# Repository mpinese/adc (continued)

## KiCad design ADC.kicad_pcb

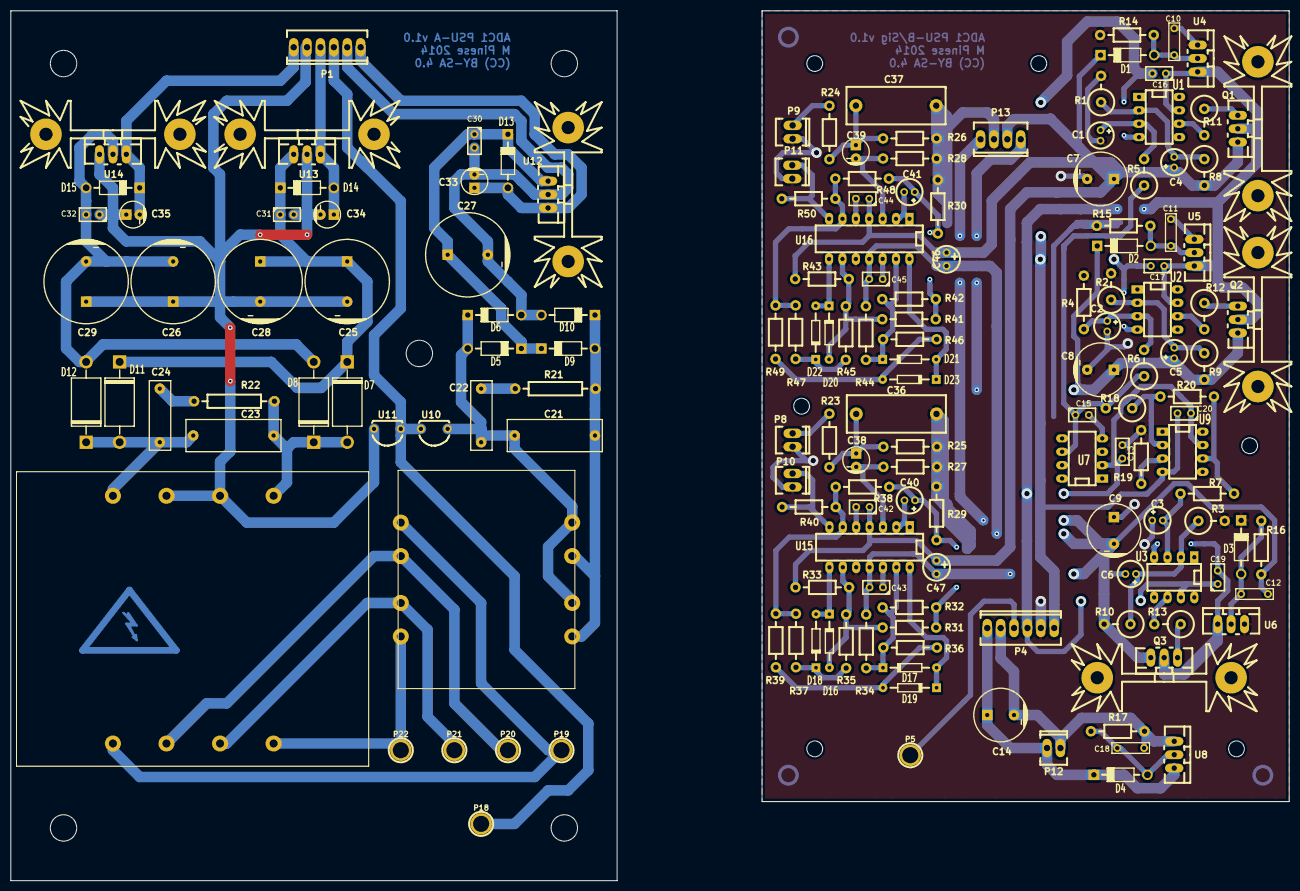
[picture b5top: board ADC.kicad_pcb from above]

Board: 4 copper layers, 242.5 x 165.0 mm, 188 parts (1 on the bottom side), 74 nets.

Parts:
C1, C3, C4, C5, C6: 10u; Elko_vert_DM5_RM2
C2, C40, C41: 47u; Elko_vert_DM5_RM2
C7, C8, C9, C14: 470u; Capacitor10x16RM5
C10, C11, C12, C18: 47n; Capacitor7.5MMDiscRM5
C13, C15, C16, C17, C19, C20, C30, C31, C32, C42, C43, C44, C45: 470n; Capacitor3MMDiscRM2.5
C21, C23: 150n; Capacitor18x6RM15
C22, C24: 10n; Capacitor13x4RM10
C25, C26, C27, C28, C29: 2700u; Capacitor16x25RM7.5
C33, C34, C35: 1u; Capacitor5x6RM2.5
C36, C37: 6.2n; Capacitor18x7RM15
C38, C39: 22u; Capacitor5x11RM2.5
C46, C47: 10u; Elko_vert_DM5_RM2-5
D1, D3: 1N4745; Diode_DO-41_SOD81_Horizontal_RM10
D2: 1N4731; Diode_DO-41_SOD81_Horizontal_RM10
D4: 1N4734; Diode_DO-41_SOD81_Horizontal_RM10
D5, D6, D9, D10, D13, D14, D15: 1N4001; Diode_DO-41_SOD81_Horizontal_RM10
D7, D8, D11, D12: RL205; Diode_DO-201AD_Horizontal_RM15
D16, D17, D18, D19, D20, D21, D22, D23: 1N4148; Diode_DO-35_SOD27_Horizontal_RM10
F1: FUSE; Dummy_Empty
FID: Fiducial_Modern_CopperBottom_RevC; Fiducial_Modern_CopperBottom
FID#2, FID#3: Fiducial_Modern_CopperBottom_RevC; Fiducial_Modern_CopperBottom
HS: Heatsink_Fischer_SK104-STC-STIC_35x13mm_2xDrill2.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; Heatsink_Fischer_SK104-STC-STIC_35x13mm_2xDrill2.5mm
HS#2, HS#3, HS#4, HS#5, HS#6: Heatsink_Fischer_SK104-STC-STIC_35x13mm_2xDrill2.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; Heatsink_Fischer_SK104-STC-STIC_35x13mm_2xDrill2.5mm
J1, J2: RCA; Dummy_Empty
J3: IEC-C13-SOCKET; Dummy_Empty
MH: MountingHole_5mm_RevA_Date21Jun2010; MountingHole_5mm
MH#2, MH#3, MH#4, MH#5: MountingHole_5mm_RevA_Date21Jun2010; MountingHole_5mm
MH#6, MH#7, MH#8, MH#9, MH#10, MH#11: MountingHole_3mm_RevA_Date21Jun2010; MountingHole_3mm
P1, P4: CONN_6; Socket_MOLEX-KK-RM2-54mm_Lock_6pin_straight
P2, P3: CONN_6; Dummy_Empty
P5, P18, P19, P20, P21, P22: CONN_1; 1pin
P6, P7, P14, P15, P16: CONN_2; Dummy_Empty
P8, P9, P10, P11, P12: CONN_2; Socket_MOLEX-KK-RM2-54mm_Lock_2pin_straight
P13: CONN_4; Socket_MOLEX-KK-RM2-54mm_Lock_4pin_straight
P17: CONN_4; Dummy_Empty
Q1, Q2: BD241A; TO-220_Neutral123_Vertical_LargePads
Q3: BD242; TO-220_Neutral123_Vertical_LargePads
R1, R2, R3, R9: 4.99k; Resistor_Vertical_RM5mm
R4, R14, R15, R16, R17: 1k; Resistor_Horizontal_RM10mm
R5: 3.32k; Resistor_Vertical_RM5mm
R6, R18: 1.5k; Resistor_Vertical_RM5mm
R7: 3.32k; Resistor_Horizontal_RM10mm
R8, R10: 10k; Resistor_Vertical_RM5mm
R11, R12, R13: 47; Resistor_Vertical_RM5mm
R19: 750; Resistor_Horizontal_RM10mm
R20: 1.5k; Resistor_Horizontal_RM10mm
R21, R22: R; Resistor_Horizontal_RM15mm
R23, R24: 56; Resistor_Horizontal_RM10mm
R25, R26, R27, R28, R29, R30: 22k; Resistor_Horizontal_RM10mm
R31, R32, R35, R36, R41, R42, R45, R46: 10k; Resistor_Horizontal_RM10mm
R33, R34, R43, R44: 24k; Resistor_Horizontal_RM10mm
R37, R38, R39, R40, R47, R48, R49, R50: 2.2k; Resistor_Horizontal_RM10mm
Sym: Symbol_Highvoltage_Type2_CopperTop_Small
T1: TRIAD-FS20-300-C2; TRIAD_FS16_400_C2
T2: TRIAD-FS48-750-C2; TRIAD_FS48_750_C2
U1, U2, U3, U9: OPA27; DIP-8__300_ELL
U4, U5, U6, U8: 2N6507; TO-220_Neutral123_Vertical_LargePads
U7: REF02; DIP-8__300_ELL
U10, U11: P0300ECL; TO-92-Free-inline-wide
U12: MC7805C; TO-220_Neutral123_Vertical_LargePads
U13: LM7818CT; TO-220_Neutral123_Vertical_LargePads
U14: LM7918CT; TO-220_Neutral123_Vertical_LargePads
U15, U16: LME49740; DIP-14__300_ELL

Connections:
/Clipper/+15V: C4.1, C7.1, C42.1, C44.1, C46.1, C47.1, D1.2, P13.2, Q1.3, R8.2, R33.2, R43.2, U15.4, U16.4
/Clipper/-15V: C6.2, C9.2, C12.2, C43.2, C45.2, C46.2, C47.2, P13.4, Q3.3, R10.2, R16.2, R34.1, R44.1, U15.11, U16.11
/Clipper/AGND: C1.2, C2.2, C3.1, C7.2, C8.2, C9.1, C10.2, C11.2, C13.2, C15.2, C36.2, C37.2, C42.2, C43.1, C44.2, C45.1, D3.2, P4.5, P8.2, P9.2, P10.2, P11.2, P13.3, R1.2, R2.2, R3.2, R4.2, R14.2, R15.2, R19.2, R25.2, R26.2, R27.2, R28.2, R29.2, R30.2, U4.1, U5.1, U6.3, U7.4, U15.5, U15.10, U15.12, U16.5, U16.10, U16.12
/Clipper/LIN: C40.1, R29.1, R31.1, R32.1, R38.1
/Clipper/LOUT: P10.1, R40.2, U15.7
/Clipper/RIN: C41.1, R30.1, R41.1, R42.1, R48.1
/Clipper/ROUT: P11.1, R50.2, U16.7
/Line Receiver/LIN: P8.1, R23.1
/Line Receiver/RIN: P9.1, R24.1
/PSU-external/+5V_EXT: C33.1, D13.1, P1.1, U12.3
/PSU-external/+18V_EXT: C34.1, D14.1, P1.4, U13.3
/PSU-external/-18V_EXT: C35.2, D15.2, P1.6, U14.3
/PSU-external/AGND_EXT: C25.2, C26.1, C28.2, C29.1, C31.2, C32.1, C34.2, C35.1, P1.5, T2.6, T2.7, U11.3, U13.2, U14.1
/PSU-external/DGND_EXT: C27.2, C30.2, C33.2, D6.1, D10.1, P1.2, U12.2
/PSU-external/PA1: P19.1, T1.1, T2.1
/PSU-external/PA2: P20.1, T1.2, T2.2
/PSU-external/PB1: P21.1, T1.3, T2.3
/PSU-external/PB2: P22.1, T1.4, T2.4
/PSU-external/SAF_GND: P1.3, P18.1, U10.3, U11.1
/PSU-external/SEC1: C23.2, C24.2, D11.1, D12.2, T2.5
/PSU-external/SEC2: C23.1, D7.1, D8.2, R22.2, T2.8
/PSU-external/SEC3: C21.2, C22.2, D5.1, D6.2, T1.5, T1.7, U10.1
/PSU-external/SEC4: C21.1, D9.1, D10.2, R21.2, T1.6, T1.8
/PSU-external/SEC6: C22.1, R21.1
/PSU-external/SEC7: C24.1, R22.1
/PSU-internal/+4V: C5.1, C8.1, D2.2, P13.1, Q2.3, R9.2
/PSU-internal/+5V: C14.1, D4.2, P4.1, P12.1, U8.3
/PSU-internal/+18V_EXT: C13.1, C16.1, C17.1, C19.1, C20.1, P4.4, Q1.2, Q2.2, U1.7, U2.7, U3.7, U4.3, U5.3, U7.2, U9.7
/PSU-internal/-18V_EXT: C16.2, C17.2, C19.2, C20.2, P4.6, Q3.2, U1.4, U2.4, U3.4, U6.1, U9.4
/PSU-internal/DGND: C14.2, C18.2, P4.2, P12.2, R17.2, U8.1
/PSU-internal/VREF+: C15.1, R5.1, R6.1, R18.2, U7.6
/PSU-internal/VREF-: R7.1, R20.1, U9.6
unnamed: C1.1, R5.2, U1.3
unnamed: C2.1, R4.1, R6.2, U2.3
unnamed: C3.2, R7.2, U3.3
unnamed: C4.2, R1.1, R8.1, U1.2
unnamed: C5.2, R2.1, R9.1, U2.2
unnamed: C6.1, R3.1, R10.1, U3.2
unnamed: C10.1, D1.1, R14.1, U4.2
unnamed: C11.1, D2.1, R15.1, U5.2
unnamed: C12.1, D3.1, R16.1, U6.2
unnamed: C18.1, D4.1, R17.1, U8.2
unnamed: C25.1, C28.1, C31.1, D7.2, D11.2, D14.2, U13.1
unnamed: C26.2, C29.2, C32.2, D8.1, D12.1, D15.1, U14.2
unnamed: C27.1, C30.1, D5.2, D9.2, D13.2, U12.1
unnamed: C36.1, C38.1, R23.2, R25.1
unnamed: C37.1, C39.1, R24.2, R26.1
unnamed: C38.2, R27.1, U15.3
unnamed: C39.2, R28.1, U16.3
unnamed: C40.2, U15.1, U15.2
unnamed: C41.2, U16.1, U16.2
unnamed: D16.1, R31.2, R33.1, R35.1, U15.9
unnamed: D16.2, D18.1, U15.8
unnamed: D17.1, D19.2, U15.14
unnamed: D17.2, R32.2, R34.2, R36.1, U15.13
unnamed: D18.2, R35.2, R37.1
unnamed: D19.1, R36.2, R39.1
unnamed: D20.1, R41.2, R43.1, R45.1, U16.9
unnamed: D20.2, D22.1, U16.8
unnamed: D21.1, D23.2, U16.14
unnamed: D21.2, R42.2, R44.2, R46.1, U16.13
unnamed: D22.2, R45.2, R47.1
unnamed: D23.1, R46.2, R49.1
unnamed: P4.3, P5.1
unnamed: Q1.1, R11.1
unnamed: Q2.1, R12.1
unnamed: Q3.1, R13.1
unnamed: R11.2, U1.6
unnamed: R12.2, U2.6
unnamed: R13.2, U3.6
unnamed: R18.1, R20.2, U9.2
unnamed: R19.1, U9.3
unnamed: R37.2, R38.2, R39.2, R40.1, U15.6
unnamed: R47.2, R48.2, R49.2, R50.1, U16.6

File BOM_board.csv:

"Id";"Designator";"Package";"Quantity";"Designation";"Supplier and ref";
1;"MH,MH,MH,MH,MH";"Mounting_Holes:MountingHole_5mm";5;"MountingHole_5mm_RevA_Date21Jun2010";;;
2;"C1,C3,C4,C5,C6";"Capacitors_Elko_ThroughHole:Elko_vert_DM5_RM2";5;"10u";;;
3;"C2,C40,C41";"Capacitors_Elko_ThroughHole:Elko_vert_DM5_RM2";3;"47u";;;
4;"C7,C8,C9,C14";"Capacitors_ThroughHole:Capacitor10x16RM5";4;"470u";;;
5;"C10,C11,C12,C18";"Capacitors_ThroughHole:Capacitor7.5MMDiscRM5";4;"47n";;;
6;"C13,C15,C16,C17,C19,C20,C30,C31,C32,C42,C43,C44,C45";"Capacitors_ThroughHole:Capacitor3MMDiscRM2.5";13;"470n";;;
7;"C21,C23";"Capacitors_ThroughHole:Capacitor18x6RM15";2;"150n";;;
8;"C22,C24";"Capacitors_ThroughHole:Capacitor13x4RM10";2;"10n";;;
9;"C25,C26,C27,C28,C29";"Capacitors_ThroughHole:Capacitor16x25RM7.5";5;"2700u";;;
10;"C33,C34,C35";"Capacitors_ThroughHole:Capacitor5x6RM2.5";3;"1u";;;
11;"C36,C37";"Capacitors_ThroughHole:Capacitor18x7RM15";2;"6.2n";;;
12;"C38,C39";"Capacitors_ThroughHole:Capacitor5x11RM2.5";2;"22u";;;
13;"D1,D3";"Diodes_ThroughHole:Diode_DO-41_SOD81_Horizontal_RM10";2;"1N4745";;;
14;"D2";"Diodes_ThroughHole:Diode_DO-41_SOD81_Horizontal_RM10";1;"1N4731";;;
15;"D4";"Diodes_ThroughHole:Diode_DO-41_SOD81_Horizontal_RM10";1;"1N4734";;;
16;"D5,D6,D9,D10,D13,D14,D15";"Diodes_ThroughHole:Diode_DO-41_SOD81_Horizontal_RM10";7;"1N4001";;;
17;"D7,D8,D11,D12";"Diodes_ThroughHole:Diode_DO-201AD_Horizontal_RM15";4;"RL205";;;
18;"D16,D17,D18,D19,D20,D21,D22,D23";"Diodes_ThroughHole:Diode_DO-35_SOD27_Horizontal_RM10";8;"1N4148";;;
19;"P1,P4";"Sockets_MOLEX_KK-System:Socket_MOLEX-KK-RM2-54mm_Lock_6pin_straight";2;"CONN_6";;;
20;"P5,P18,P19,P20,P21,P22";"Connect:1pin";6;"CONN_1";;;
21;"P8,P9,P10,P11,P12";"Sockets_MOLEX_KK-System:Socket_MOLEX-KK-RM2-54mm_Lock_2pin_straight";5;"CONN_2";;;
22;"P13";"Sockets_MOLEX_KK-System:Socket_MOLEX-KK-RM2-54mm_Lock_4pin_straight";1;"CONN_4";;;
23;"Q1,Q2";"Transistors_TO-220:TO-220_Neutral123_Vertical_LargePads";2;"BD241A";;;
24;"Q3";"Transistors_TO-220:TO-220_Neutral123_Vertical_LargePads";1;"BD242";;;
25;"R15,R16,R17,R4,R14";"Resistors_ThroughHole:Resistor_Horizontal_RM10mm";5;"1k";;;
26;"R19";"Resistors_ThroughHole:Resistor_Horizontal_RM10mm";1;"750";;;
27;"R20";"Resistors_ThroughHole:Resistor_Horizontal_RM10mm";1;"1.5k";;;
28;"R21,R22";"Resistors_ThroughHole:Resistor_Horizontal_RM15mm";2;"R";;;
29;"R23,R24";"Resistors_ThroughHole:Resistor_Horizontal_RM10mm";2;"56";;;
30;"R25,R26,R27,R28,R29,R30";"Resistors_ThroughHole:Resistor_Horizontal_RM10mm";6;"22k";;;
31;"R31,R32,R35,R36,R41,R42,R45,R46";"Resistors_ThroughHole:Resistor_Horizontal_RM10mm";8;"10k";;;
32;"R37,R38,R39,R40,R47,R48,R49,R50";"Resistors_ThroughHole:Resistor_Horizontal_RM10mm";8;"2.2k";;;
33;"R43,R44,R34,R33";"Resistors_ThroughHole:Resistor_Horizontal_RM10mm";4;"24k";;;
34;"T1";"my-trafos:TRIAD_FS16_400_C2";1;"TRIAD-FS20-300-C2";;;
35;"T2";"my-trafos:TRIAD_FS48_750_C2";1;"TRIAD-FS48-750-C2";;;
36;"U4,U5,U6,U8";"Transistors_TO-220:TO-220_Neutral123_Vertical_LargePads";4;"2N6507";;;
37;"U7";"Sockets_DIP:DIP-8__300_ELL";1;"REF02";;;
38;"U10,U11";"Housings_TO-92:TO-92-Free-inline-wide";2;"P0300ECL";;;
39;"U12";"Transistors_TO-220:TO-220_Neutral123_Vertical_LargePads";1;"MC7805C";;;
40;"U13";"Transistors_TO-220:TO-220_Neutral123_Vertical_LargePads";1;"LM7818CT";;;
41;"U14";"Transistors_TO-220:TO-220_Neutral123_Vertical_LargePads";1;"LM7918CT";;;
42;"U15,U16";"Sockets_DIP:DIP-14__300_ELL";2;"LME49740";;;
43;"HS,HS,HS,HS,HS,HS";"Heatsinks:Heatsink_Fischer_SK104-STC-STIC_35x13mm_2xDrill2.5mm";6;"Heatsink_Fischer_SK104-STC-STIC_35x13mm_2xDrill2.5mm";;;
44;"Sym";"Footprint_Symbols:Symbol_Highvoltage_Type2_CopperTop_Small";1;"Symbol_Highvoltage_Type2_CopperTop_Small";;;
45;"U1,U2,U3,U9";"Sockets_DIP:DIP-8__300_ELL";4;"OPA27";;;
46;"R11,R13,R12";"Resistors_ThroughHole:Resistor_Vertical_RM5mm";3;"47";;;
47;"R8,R10";"Resistors_ThroughHole:Resistor_Vertical_RM5mm";2;"10k";;;
48;"R1,R3,R9,R2";"Resistors_ThroughHole:Resistor_Vertical_RM5mm";4;"4.99k";;;
49;"R5";"Resistors_ThroughHole:Resistor_Vertical_RM5mm";1;"3.32k";;;
50;"R6,R18";"Resistors_ThroughHole:Resistor_Vertical_RM5mm";2;"1.5k";;;
51;"R7";"Resistors_ThroughHole:Resistor_Horizontal_RM10mm";1;"3.32k";;;
52;"C46,C47";"Capacitors_Elko_ThroughHole:Elko_vert_DM5_RM2-5";2;"10u";;;
53;"MH,MH,MH,MH,MH,MH";"Mounting_Holes:MountingHole_3mm";6;"MountingHole_3mm_RevA_Date21Jun2010";;;
54;"FID,FID,FID";"Fiducials:Fiducial_Modern_CopperBottom";3;"Fiducial_Modern_CopperBottom_RevC";;;
55;"F1";"Oddities:Dummy_Empty";1;"FUSE";;;
56;"J1,J2";"Oddities:Dummy_Empty";2;"RCA";;;
57;"J3";"Oddities:Dummy_Empty";1;"IEC-C13-SOCKET";;;
58;"P2,P3";"Oddities:Dummy_Empty";2;"CONN_6";;;
59;"P6,P7,P14,P15,P16";"Oddities:Dummy_Empty";5;"CONN_2";;;
60;"P17";"Oddities:Dummy_Empty";1;"CONN_4";;;

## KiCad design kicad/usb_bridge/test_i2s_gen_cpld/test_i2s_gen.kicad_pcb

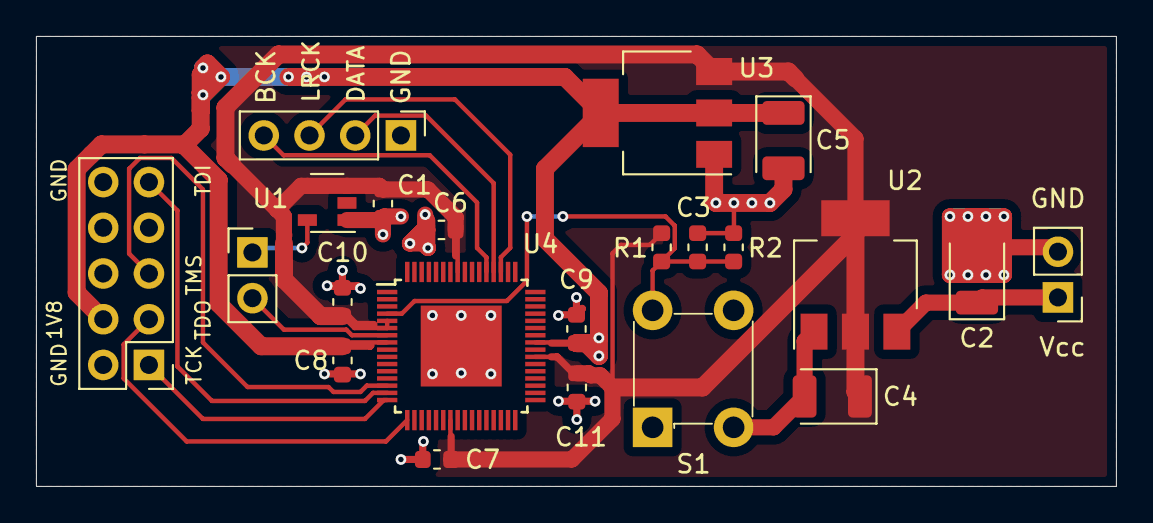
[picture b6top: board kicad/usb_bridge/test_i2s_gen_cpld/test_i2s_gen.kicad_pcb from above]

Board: 2 copper layers, 60.0 x 25.0 mm, 22 parts (0 on the bottom side), 14 nets.

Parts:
C1, C6, C7, C8, C9, C10, C11: 100n; C_0603_1608Metric
C2, C4, C5: CP; CP_EIA-3528-21_Kemet-B
C3: 470n; C_0603_1608Metric
J1, J3: Conn_01x02_Male; PinHeader_1x02_P2.54mm_Vertical
J2: Conn_02x05_Odd_Even; PinHeader_2x05_P2.54mm_Vertical
J4: Conn_01x04_Male; PinHeader_1x04_P2.54mm_Vertical
R1: 14k; R_0603_1608Metric
R2: 21k; R_0603_1608Metric
S1: 1825910-6; Switch_Tactile_THT_6x6mm
U1: SIT2001B; SOT-23-5
U2: AMS1117-3.3; SOT-223-3_TabPin2
U3: AMS1117-1.8; SOT-223-3_TabPin2
U4: 5M40ZE64C5N; TQFP-64_7x7mm_P0.4mm_EP4.5x4.5mm

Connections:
+1V8: C5.1, C8.1, C9.1, J2.4, U3.2, U4.8, U4.41
+3V3: C1.1, C4.1, C6.1, C7.1, C10.1, C11.1, R1.2, U1.3, U1.4, U2.2, U3.3, U4.5, U4.6, U4.23, U4.39, U4.57
/BCK: J4.4, U4.53
/CLK12: J3.2, U4.7
/DATA: J4.2, U4.52
/LRCK: J4.3, U4.51
/TCK: J2.1, U4.16
/TDI: J2.9, U4.15
/TDO: J2.3, U4.17
/TMS: J2.5, U4.14
/Vcc: C2.1, J1.1, U2.3
/~RESET: C3.1, R1.1, R2.2, S1.2, U4.4
GNDD: C1.2, C2.2, C3.2, C4.2, C5.2, C6.2, C7.2, C8.2, C9.2, C10.2, C11.2, J1.2, J2.2, J2.10, J4.1, R2.1, S1.3, S1.4, U1.1, U2.1, U3.1, U4.65
unnamed: J3.1, U1.5

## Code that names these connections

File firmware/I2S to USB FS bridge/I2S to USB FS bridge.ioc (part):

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Mcu.Name=STM32F730R8Tx
Mcu.Package=LQFP64
Mcu.UserName=STM32F730R8Tx
PA11.Mode=Device_Only
PA11.Signal=USB_OTG_FS_DM
PA12.Mode=Device_Only
PA12.Signal=USB_OTG_FS_DP
PA13.Mode=Serial_Wire
PA13.Signal=SYS_JTMS-SWDIO
PA14.Mode=Serial_Wire
PA14.Signal=SYS_JTCK-SWCLK
PA2.Mode=Asynchronous
PA2.Signal=USART2_TX
PA3.Mode=Asynchronous
PA3.Signal=USART2_RX
PA9.Mode=Activate_VBUS
PA9.Signal=USB_OTG_FS_VBUS
PB10.Mode=Half_Duplex_Slave
PB10.Signal=I2S2_CK
PB12.Mode=Half_Duplex_Slave
PB12.Signal=I2S2_WS
PC1.Mode=Half_Duplex_Slave
PC1.Signal=I2S2_SD
PC6.Signal=GPIO_Output
PC7.Signal=GPIO_Output
PC8.Signal=GPIO_Output
PC9.Signal=GPIO_Output
PH0-OSC_IN.Mode=HSE-External-Clock-Source
PH0-OSC_IN.Signal=RCC_OSC_IN
PH1-OSC_OUT.Mode=HSE-External-Clock-Source
PH1-OSC_OUT.Signal=RCC_OSC_OUT
RCC.HSE_VALUE=16000000
RCC.SYSCLKFreq_VALUE=216000000
RCC.SYSCLKSource=RCC_SYSCLKSOURCE_PLLCLK
board=custom

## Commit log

2014-05-04 Initial commit. Power supply mostly done; nothing else.
2014-05-04 Added the library cache file.
2014-05-05 Started on parts selection.
2014-05-06 Started work on changing the PSU to fully complementary.
2014-05-06 Started splitting the PSU into internal and external subsections.
2014-05-07 Simplified external PSU, now that I've decided to put it in its own case.
2014-05-09 Added an analysis of the low pass filter present in the PCM4222EVM differential input stage.
2014-05-10 Completed the overall system layout, added clipping and input stages.
2014-05-10 Further PSU tweaking for extra safety, added a TODO list.
2014-05-12 Expanded the internal PSU to include a 4 V supply. Started on reference sharing.
2014-05-12 Cleaned up the internal PSU a bit.
2014-05-15 Many additions; the system's almost together. Just need to tidy up a few things around the PSU and the input stage.
2014-05-21 First complete system. Still a few things to check.
2014-05-21 Noise analysis completed; signal section finished.
2014-05-21 V1.0 Schematic Completed.
2014-05-21 Added tag Schematic 1.0 for changeset 5b91ce586c58
2014-05-21 Added component numbers.
2014-05-21 Removed tag Schematic 1.0
2014-05-21 Added tag 1.0 Schematic for changeset b9613084385d
2014-05-21 Removed tag 1.0 Schematic
2014-05-21 Started specifying packages.
2014-05-21 More packages specified; changed the external PSU overvoltage protection devices.
2014-05-21 More packages specified.
2014-05-22 Minor schematic mods, started assigning DigiKey part numbers to components.
2014-05-22 Added more DigiKey catalogue numbers.
2014-05-23 Minor changes to noise sim.
2014-05-23 Further component specifications for the BOM.
2014-05-26 More components specified
2014-05-28 Completed component product code specification; started on footprints.
2014-05-29 Moved to new version of KiCad with updated footprints. Changed most of the footprints to match.
2014-05-29 Specified a few more components. These aren't perfect matches, but should do.
2014-05-30 Added internal connectors; specified all footprints and part IDs except for the trafos.
2014-05-30 More footprint specification and connector additions; almost done.
2014-05-31 Changed from the P0720ECL SIDACtor to the more sensitive P0300.
2014-05-31 Changed to use the fixed IEC socket device; the PSU netlist should now be (more) correct.
2014-06-01 A lot of routing, some parts changes: * Added snubber C/RC snubbers to transformer secondaries. * Changed PSU OA from OPA209 to OPA27. * Routed external PSU. * Mostly done routing internal circuits. 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
2014-06-02 First complete version. * Added 10uF decoupling capacitors to the start of each signal processing section. * Completed routing. A few -18 V nets remain unrouted; these will be wired in.
2014-06-03 Routed the -18 V line, added licence and descriptive text.
2014-06-03 Started work on a print SVG of the board layout.
2014-06-04 Added vias for ground-connected pins that cannot be soldered from the top, as I can't make PTHs. Rearranged the power inputs slightly.
2014-06-04 Filled in the ground plane this time -- oops!
2014-06-04 Minor ground rerouting.
2014-06-06 Collected layouts into a transparency svg. Created board and schematic BOMs (these still need to be fused)
2014-06-08 Moved component designators on silkscreen so that they are not covered by components. Combined silkscreen and user top layers into a cover layer for printing.
2014-06-09 Created script to collate final BOM.
2020-09-04 Update to 2020!
2020-09-04 Cleaning
2020-09-04 Fixed gitignore Tina-TI autosave exclusion
2020-09-11 Schematic bugfixes
2020-09-11 Firmware initial commit
2020-09-11 Cleaning up
2020-09-11 Attempted USB fixes
2020-09-12 ^&*%#$^&* copy-pasta!!!!
2020-09-13 Started adding class functionality.
2020-09-13 Restored GetHSConfigDescriptor, which seems to be necessary for successful enum (on Win10 at least).
2020-09-13 Added basic control signals.
2020-09-15 Started writing state machine for main I2S -> USB controller.
2020-09-15 More state machine work.
2020-09-15 Switched to left-justified audio input
2020-09-18 Added I2S test signal generator circuit.
2020-09-18 Added debug messages to USB loop.
2020-09-18 Added preregs to all rails.
2020-09-21 Started changing test generator to CPLD design
2020-09-21 Added TODO to enclosure SVG
2020-09-21 Restored serial audio test generator discrete design from #cee2e1e
2020-09-29 Fixed error in silkscreen
2020-10-01 Tweaks to USB code, works on linux but not Windows (suspect driver issue)
2020-10-01 I2S test generator refinements
2020-10-01 Falling back to polling I2S
2020-10-02 I2S polling roughly working.
2020-10-02 Fixed bug in overrun detection code. Fixed bug due to error in HAL_I2S_Receive docs (size to read is in 32-bit words, not 16-bit as given in the docs). Reduced i2s buffer size for testing. Added some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
2020-10-03 First rough working version. Sync issues on i2s.
2020-10-03 Renamed some status flags
2020-10-03 Added a break on error
2020-10-03 Got DMA half working. Dependence on MAX_USB_XFERSIZE noted.
2020-10-06 Moved to counter for I2S test generator.
2020-10-06 I2S counter test VHDL very roughly done
2020-10-06 I2S test counter done
2020-10-10 Now have successful streaming acquisition (single-channel only). Halt & restart still broken.
2020-10-12 I2S sync issues, not yet resolved
2020-10-14 USB protocol refinements, debugging
2020-10-17 Dramatically simplified USB code to single upload; first working version?
2020-10-17 Reduced buffer size to increase responsiveness.
2020-10-20 Basic spectrum analyser & metrics reporter
2020-10-25 Very rough working spectrum analyser server - client setup
2020-10-25 Increased sampling speed.
2020-12-01 Normalised FFT in bridge. GUI work.
